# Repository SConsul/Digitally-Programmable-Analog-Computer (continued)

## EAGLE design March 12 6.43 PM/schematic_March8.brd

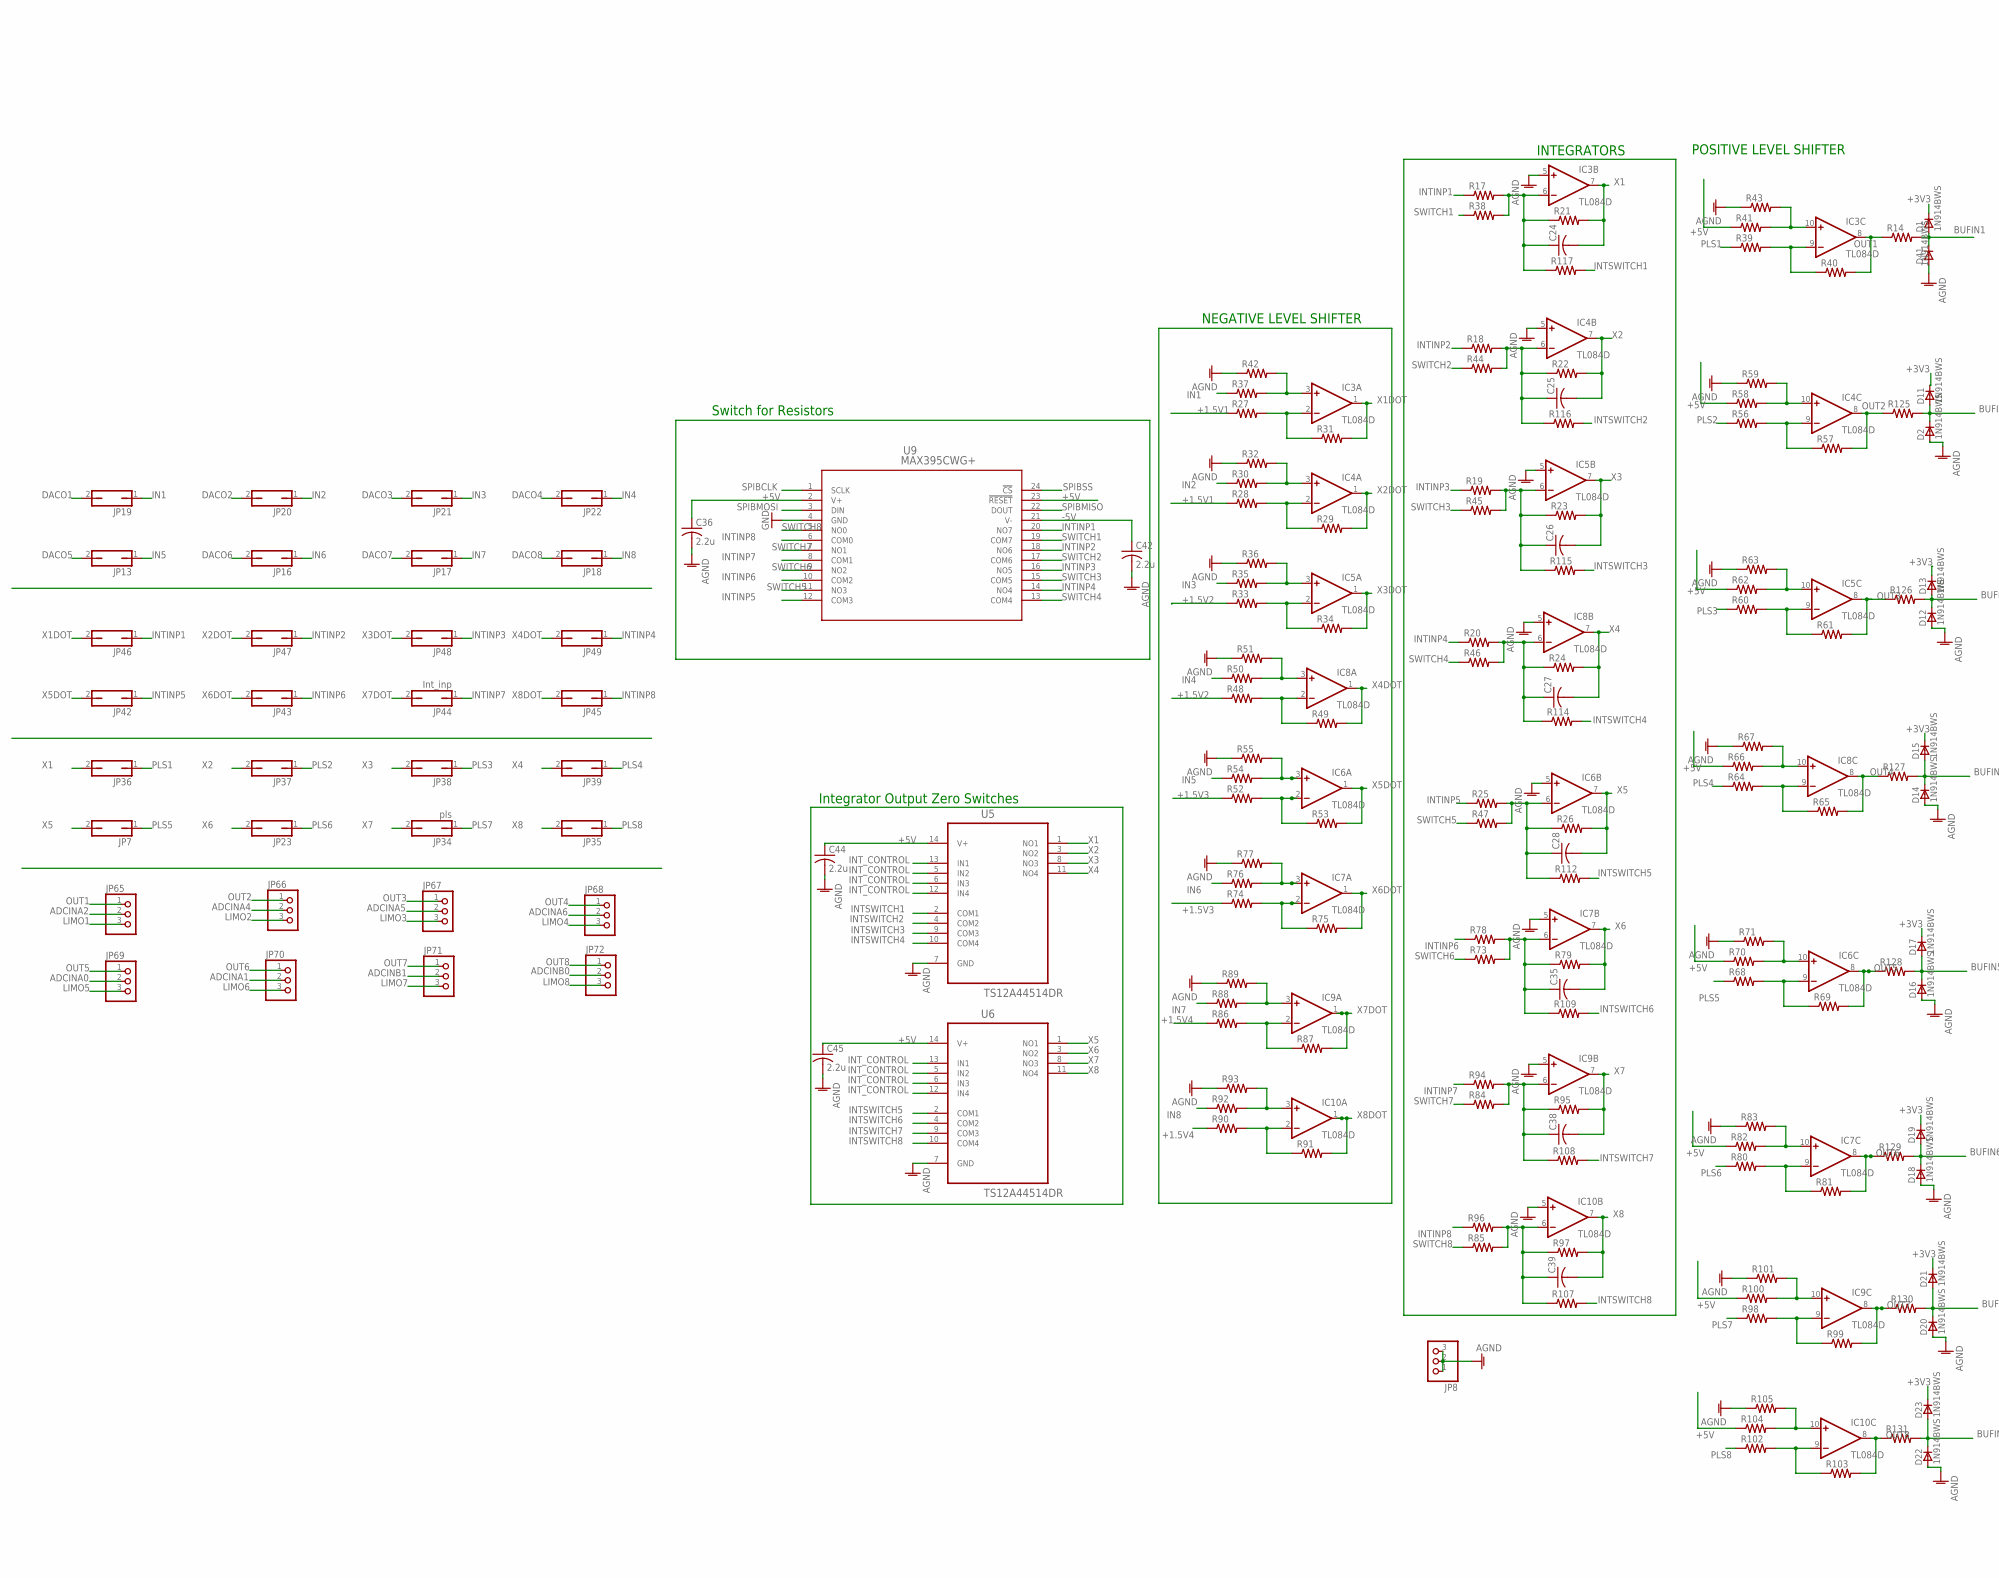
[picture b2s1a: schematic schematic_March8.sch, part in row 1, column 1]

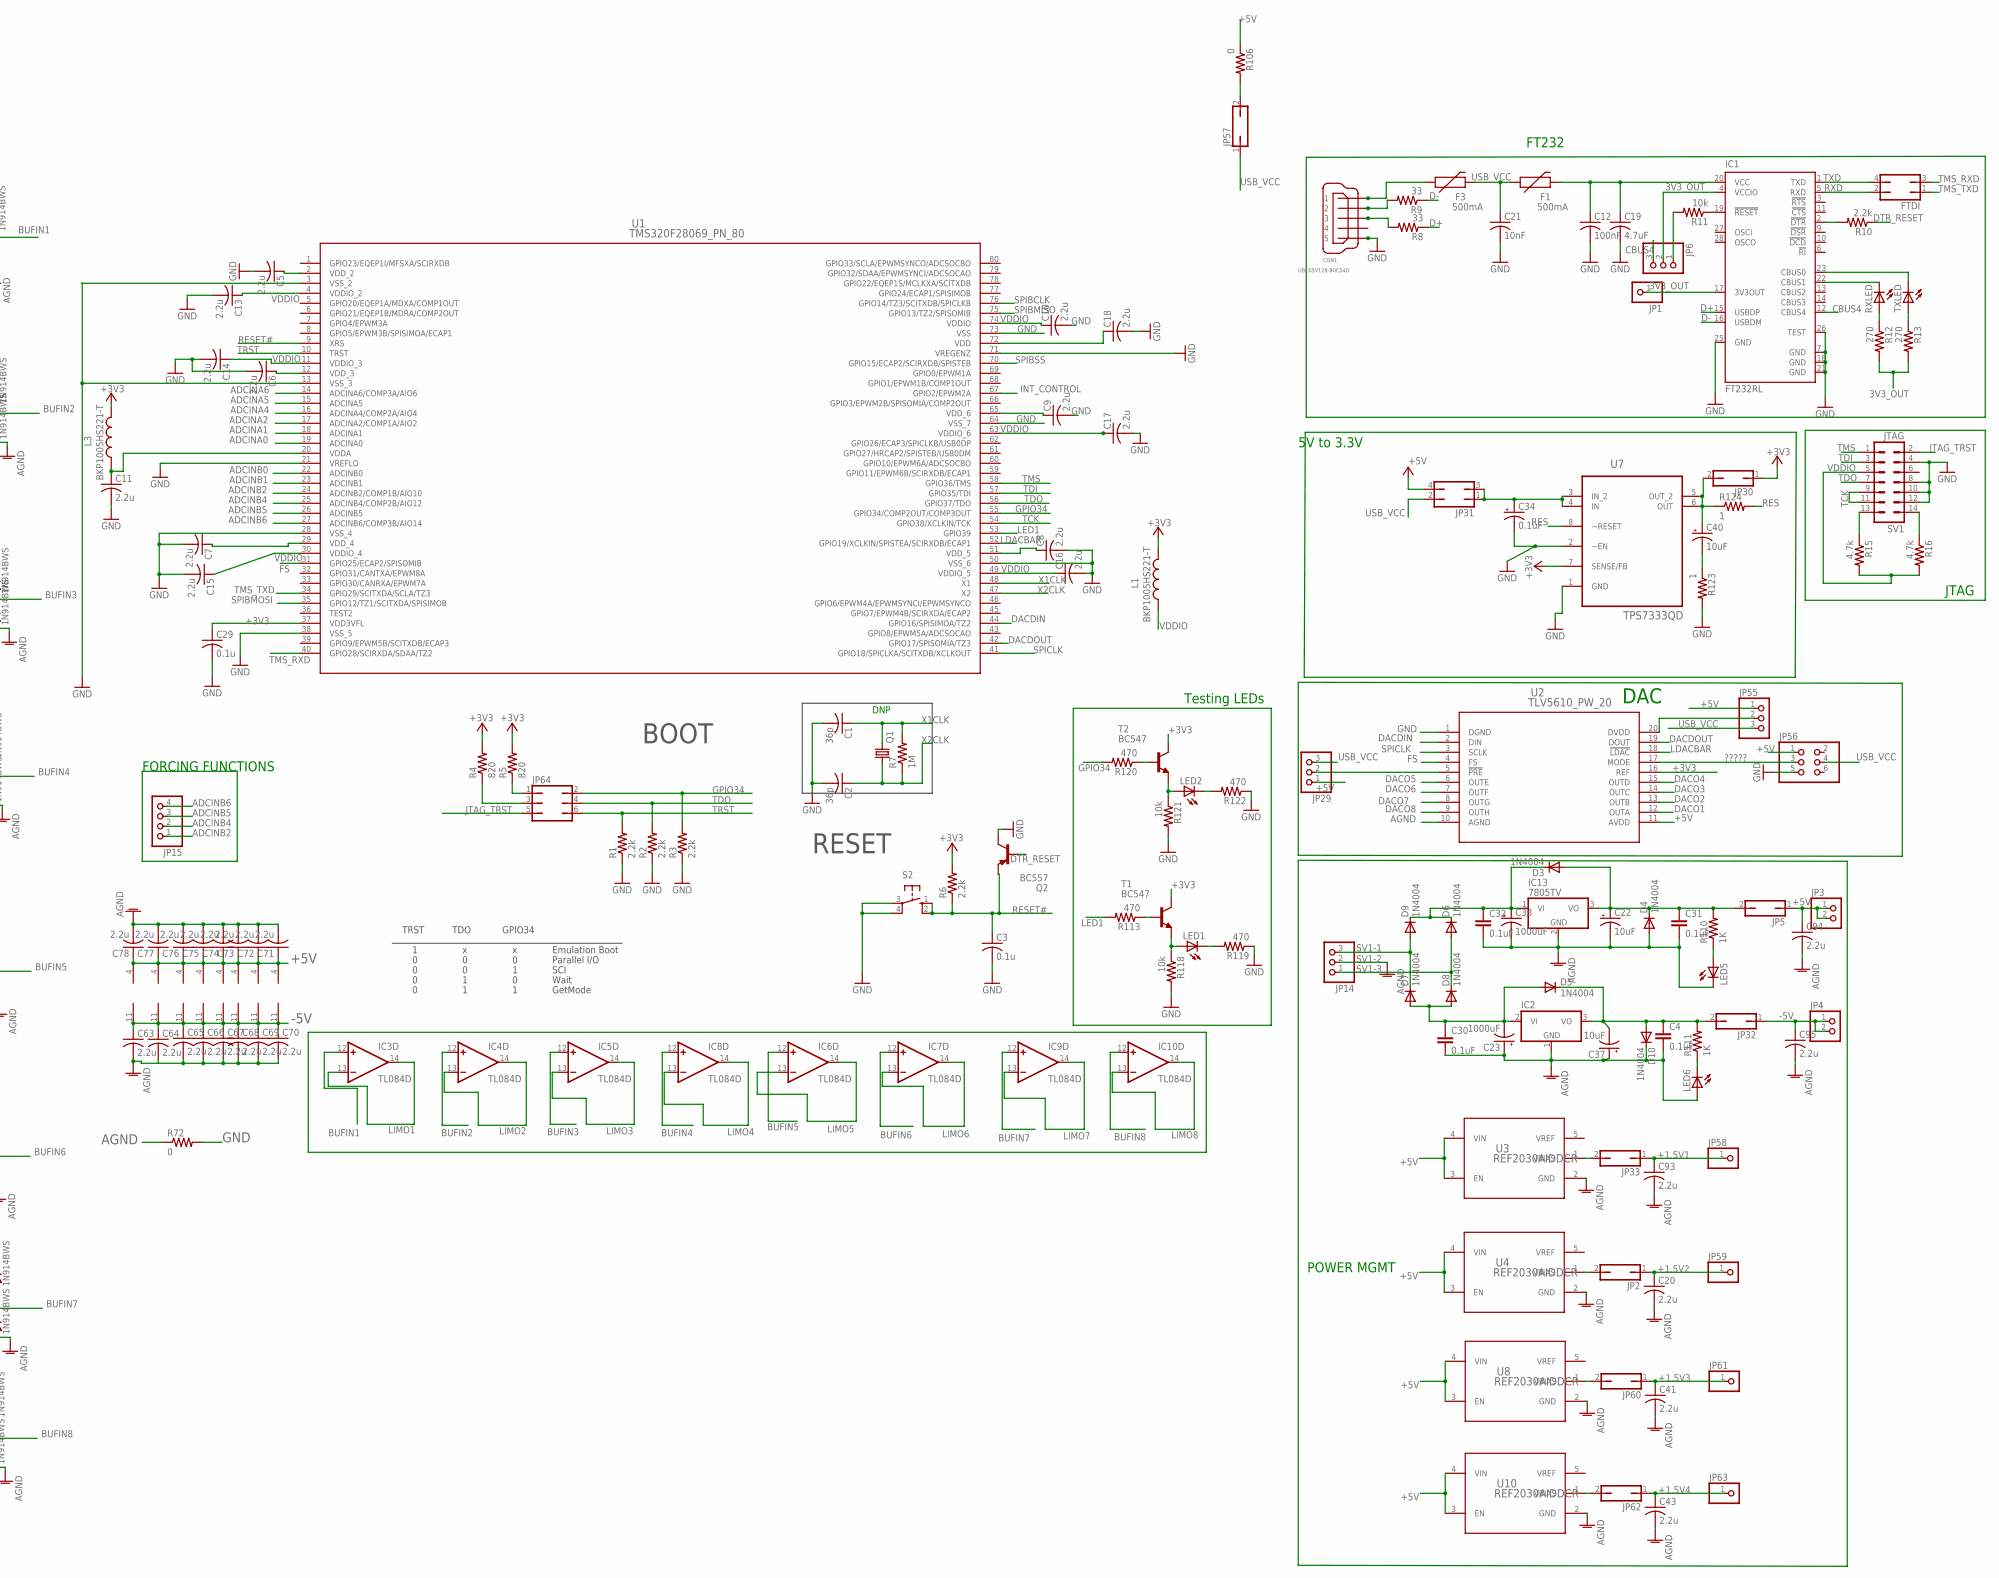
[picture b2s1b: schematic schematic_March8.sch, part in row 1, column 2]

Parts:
C1, C2: 36p; C1206
C3, C29: 0.1u; C1206
C4, C30, C31, C32: 0.1uF; C1206
C5, C6, C7, C8, C9, C10, C11, C13, C14, C15, C16, C17, C18, C20, C36, C41, C42, C43, C44, C45, C63, C64, C65, C66, C67, C68, C69, C70, C71, C72, C73, C74, C75, C76, C77, C78, C93, C94, C95: 2.2u; C1206
C12: 100nF; C1206
C19: 4.7uF; C1206
C21: 10nF; C1206
C22, C37, C40: 10uF; E2,5-7
C23, C33: 1000uF; E2,5-7
C24, C25, C26, C27, C28, C35, C38, C39: C-USC1206; C1206
C34: 0.1uF; E2,5-7
CON1: UBC05V128-B0C04D; 32005-201
D1, D2, D11, D12, D13, D14, D15, D16, D17, D18, D19, D20, D21, D22, D23, D41: 1N914BWS; SOD323F
D3, D4, D5, D6, D7, D8, D9, D10: 1N4004; DO41-10
F1, F3: 500mA; 0603
FTDI: JP2Q
IC1: FT232RL; SSOP28
IC2: 7905T; TO220H
IC3, IC4, IC5, IC6, IC7, IC8, IC9, IC10: TL084D; SO14
IC13: 7805TV; TO220V
JP1, JP58, JP59, JP61, JP63: PINHD-1X1; 1X01
JP2, JP5, JP7, JP13, JP16, JP17, JP18, JP19, JP20, JP21, JP22, JP23, JP30, JP32, JP33, JP35, JP36, JP37, JP38, JP39, JP42, JP43, JP45, JP46, JP47, JP48, JP49, JP57, JP60, JP62: JP1Q; JP1
JP3, JP4: PINHD-1X2; 1X02
JP6, JP8, JP14, JP29, JP55, JP65, JP66, JP67, JP68, JP69, JP70, JP71, JP72: PINHD-1X3; 1X03
JP15: PINHD-1X4; 1X04
JP31: JP2Q
JP34: pls; JP1
JP44: Int_inp; JP1
JP56: PINHD-2X3; 2X03
JP64: JP3Q
L1, L3: BKP1005HS221-T; 0204/5
LED1, LED2, LED5, LED6: LED3MM
Q1: CRYSTALHC49S; HC49/S
Q2: BC557; TO92-EBC
R1, R2, R3, R6, R10: 2.2k; R1206
R4, R5: 820; R1206
R7: 1M; R1206
R8, R9: 33; R1206
R11, R118, R121: 10k; R1206
R12, R13: 270; R1206
R14, R17, R18, R19, R20, R21, R22, R23, R24, R25, R26, R27, R28, R29, R30, R31, R32, R33, R34, R35, R36, R37, R38, R39, R40, R41, R42, R43, R44, R45, R46, R47, R48, R49, R50, R51, R52, R53, R54, R55, R56, R57, R58, R59, R60, R61, R62, R63, R64, R65, R66, R67, R68, R69, R70, R71, R73, R74, R75, R76, R77, R78, R79, R80, R81, R82, R83, R84, R85, R86, R87, R88, R89, R90, R91, R92, R93, R94, R95, R96, R97, R98, R99, R100, R101, R102, R103, R104, R105, R107, R108, R109, R112, R114, R115, R116, R117, R125, R126, R127, R128, R129, R130, R131: R-US_R1206; R1206
R15, R16: 4.7k; M1206
R72, R106: 0; R1206
R110, R111: 1K; 0207/10
R113, R119, R120, R122: 470; R1206
R123, R124: 1; M1206
RXLED: LEDCHIPLED_1206; CHIPLED_1206
S2: 10-XX; B3F-10XX
SV1: JTAG; MA07-2
T1, T2: BC547; TO92
TXLED: LEDCHIPLED_1206; CHIPLED_1206
U1: TMS320F28069_PN_80; PN80
U2: TLV5610_PW_20; PW20
U3, U4, U8, U10: REF2030AIDDCR; DDC0005A_N
U5, U6: TS12A44514DR; SOIC127P600X175-14N
U7: TPS7333QD; SOIC127P600X175-8N
U9: MAX395CWG+; 21-0042B_24

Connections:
3V3_OUT: IC1.4 (VCCIO), IC1.17 (3V3OUT), JP1.1, JP6.2, R12.2, R13.2
+1.5V1: C93.1, JP33.1, JP58.1, R27.1, R28.1
+1.5V2: C20.1, JP2.1, JP59.1, R33.1, R48.1
+1.5V3: C41.1, JP60.1, JP61.1, R52.1, R74.1
+1.5V4: C43.1, JP62.1, JP63.1, R86.1, R90.1
+3V3: C29.1, D1.C, D11.C, D13.C, D15.C, D17.C, D19.C, D21.C, D23.C, JP30.1, L1.2, L3.2, R4.2, R5.2, R6.2, T1.3 (C), T2.3 (C), U1.37 (VDD3VFL), U2.16 (REF), U7.7 (SENSE/FB)
+5V: C36.1, C44.1, C45.1, C71.1, C72.1, C73.1, C74.1, C75.1, C76.1, C77.1, C78.1, C94.1, IC3.4 (V+), IC4.4 (V+), IC5.4 (V+), IC6.4 (V+), IC7.4 (V+), IC8.4 (V+), IC9.4 (V+), IC10.4 (V+), JP3.1, JP3.2, JP5.1, JP29.1, JP31.4, JP55.1, JP56.1, R41.1, R58.1, R62.1, R66.1, R70.1, R82.1, R100.1, R104.1, R106.1, U2.11 (AVDD), U3.3 (EN), U3.4 (VIN), U4.3 (EN), U4.4 (VIN), U5.14 (V+), U6.14 (V+), U8.3 (EN), U8.4 (VIN), U9.2 (V+), U9.23 (!RESET), U10.3 (EN), U10.4 (VIN)
-5V: C42.1, C63.1, C64.1, C65.1, C66.1, C67.1, C68.1, C69.1, C70.1, C95.1, IC3.11 (V-), IC4.11 (V-), IC5.11 (V-), IC6.11 (V-), IC7.11 (V-), IC8.11 (V-), IC9.11 (V-), IC10.11 (V-), JP4.1, JP4.2, JP32.1, U9.21 (V-)
?????: JP56.3, U2.17 (MODE)
ADCINA0: JP69.2, U1.19 (ADCINA0)
ADCINA1: JP70.2, U1.18 (ADCINA1)
ADCINA2: JP65.2, U1.17 (ADCINA2/COMP1A/AIO2)
ADCINA4: JP66.2, U1.16 (ADCINA4/COMP2A/AIO4)
ADCINA5: JP67.2, U1.15 (ADCINA5)
ADCINA6: JP68.2, U1.14 (ADCINA6/COMP3A/AIO6)
ADCINB0: JP72.2, U1.22 (ADCINB0)
ADCINB1: JP71.2, U1.23 (ADCINB1)
ADCINB2: JP15.1, U1.24 (ADCINB2/COMP1B/AIO10)
ADCINB4: JP15.2, U1.25 (ADCINB4/COMP2B/AIO12)
ADCINB5: JP15.3, U1.26 (ADCINB5)
ADCINB6: JP15.4, U1.27 (ADCINB6/COMP3B/AIO14)
AGND: C4.2, C20.2, C22.-, C23.+, C30.2, C31.2, C32.2, C33.-, C36.2, C37.+, C41.2, C42.2, C43.2, C44.2, C45.2, C63.2, C64.2, C65.2, C66.2, C67.2, C68.2, C69.2, C70.2, C71.2, C72.2, C73.2, C74.2, C75.2, C76.2, C77.2, C78.2, C93.2, C94.2, C95.2, D2.A, D4.A, D10.C, D12.A, D14.A, D16.A, D18.A, D20.A, D22.A, D41.A, IC2.1 (GND), IC3.5 (+IN), IC4.5 (+IN), IC5.5 (+IN), IC6.5 (+IN), IC7.5 (+IN), IC8.5 (+IN), IC9.5 (+IN), IC10.5 (+IN), IC13.2 (GND), JP8.1, JP8.2, JP8.3, LED5.K (C), LED6.A, R32.1, R36.1, R42.1, R43.1, R51.1, R55.1, R59.1, R63.1, R67.1, R71.1, R72.1, R77.1, R83.1, R89.1, R93.1, R101.1, R105.1, U2.10 (AGND), U3.2 (GND), U4.2 (GND), U5.7 (GND), U6.7 (GND), U8.2 (GND), U10.2 (GND)
BUFIN1: D1.A, D41.C, IC3.12 (+IN), R14.2
BUFIN2: D2.C, D11.A, IC4.12 (+IN), R125.2
BUFIN3: D12.C, D13.A, IC5.12 (+IN), R126.2
BUFIN4: D14.C, D15.A, IC8.12 (+IN), R127.2
BUFIN5: D16.C, D17.A, IC6.12 (+IN), R128.2
BUFIN6: D18.C, D19.A, IC7.12 (+IN), R129.2
BUFIN7: D20.C, D21.A, IC9.12 (+IN), R130.2
BUFIN8: D22.C, D23.A, IC10.12 (+IN), R131.2
CBUS4: IC1.12 (CBUS4), JP6.3
D+: IC1.15 (USBDP), R8.1
D-: IC1.16 (USBDM), R9.1
DACDIN: U1.44 (GPIO16/SPISIMOA/TZ2), U2.2 (DIN)
DACDOUT: U1.42 (GPIO17/SPISOMIA/TZ3), U2.19 (DOUT)
DACO1: JP19.2, U2.12 (OUTA)
DACO2: JP20.2, U2.13 (OUTB)
DACO3: JP21.2, U2.14 (OUTC)
DACO4: JP22.2, U2.15 (OUTD)
DACO5: JP13.2, U2.6 (OUTE)
DACO6: JP16.2, U2.7 (OUTF)
DACO7: JP17.2, U2.8 (OUTG)
DACO8: JP18.2, U2.9 (OUTH)
DTR_RESET: Q2.B, R10.1
FS: U1.31 (GPIO25/ECAP2/SPISOMIB), U2.4 (FS)
GND: C1.2, C2.2, C3.2, C5.2, C6.2, C7.2, C8.2, C9.2, C10.2, C11.2, C12.2, C13.2, C14.2, C15.2, C16.2, C17.2, C18.2, C19.2, C21.2, C29.2, C34.-, CON1.5, IC1.7 (GND), IC1.18 (GND), IC1.21 (GND), IC1.25 (GND), IC1.26 (TEST), JP56.5, Q2.C, R1.1, R2.1, R3.1, R72.2, R118.2, R119.1, R121.2, R122.1, R123.2, S2.3, S2.4 (P1), SV1.4, SV1.8, SV1.10, SV1.12, U1.3 (VSS_2), U1.13 (VSS_3), U1.21 (VREFLO), U1.28 (VSS_4), U1.38 (VSS_5), U1.50 (VSS_6), U1.64 (VSS_7), U1.71 (VREGENZ), U1.73 (VSS), U2.1 (DGND), U7.1 (GND), U7.2 (~EN), U9.4 (GND)
GPIO34: JP64.2, R3.2, R120.2, U1.55 (GPIO34/COMP2OUT/COMP3OUT)
IDK: C22.+, C31.1, D3.A, D4.C, IC13.3 (VO), JP5.2, R110.2
IDK2: C4.1, C37.-, D5.C, D10.A, IC2.3 (VO), JP32.2, R111.2
IN1: JP19.1, R37.1
IN2: JP20.1, R30.1
IN3: JP21.1, R35.1
IN4: JP22.1, R50.1
IN5: JP13.1, R54.1
IN6: JP16.1, R76.1
IN7: JP17.1, R88.1
IN8: JP18.1, R92.1
INTINP1: JP46.1, R17.1, U9.20 (NO7)
INTINP2: JP47.1, R18.1, U9.18 (NO6)
INTINP3: JP48.1, R19.1, U9.16 (NO5)
INTINP4: JP49.1, R20.1, U9.14 (NO4)
INTINP5: JP42.1, R25.1, U9.12 (COM3)
INTINP6: JP43.1, R78.1, U9.10 (COM2)
INTINP7: JP44.1, R94.1, U9.8 (COM1)
INTINP8: JP45.1, R96.1, U9.6 (COM0)
INTSWITCH1: R117.2, U5.2 (COM1)
INTSWITCH2: R116.2, U5.4 (COM2)
INTSWITCH3: R115.2, U5.9 (COM3)
INTSWITCH4: R114.2, U5.10 (COM4)
INTSWITCH5: R112.2, U6.2 (COM1)
INTSWITCH6: R109.2, U6.4 (COM2)
INTSWITCH7: R108.2, U6.9 (COM3)
INTSWITCH8: R107.2, U6.10 (COM4)
INT_CONTROL: U1.67 (GPIO2/EPWM2A), U5.5 (IN2), U5.6 (IN3), U5.12 (IN4), U5.13 (IN1), U6.5 (IN2), U6.6 (IN3), U6.12 (IN4), U6.13 (IN1)
JTAG_TRST: JP64.5, SV1.2
LDACBAR: U1.52 (GPIO19/XCLKIN/SPISTEA/SCIRXDB/ECAP1), U2.18 (!LDAC)
LED1: R113.2, U1.53 (GPIO39)
LIMO1: IC3.13 (-IN), IC3.14 (OUT), JP65.3
LIMO2: IC4.13 (-IN), IC4.14 (OUT), JP66.3
LIMO3: IC5.13 (-IN), IC5.14 (OUT), JP67.3
LIMO4: IC8.13 (-IN), IC8.14 (OUT), JP68.3
LIMO5: IC6.13 (-IN), IC6.14 (OUT), JP69.3
LIMO6: IC7.13 (-IN), IC7.14 (OUT), JP70.3
LIMO7: IC9.13 (-IN), IC9.14 (OUT), JP71.3
LIMO8: IC10.13 (-IN), IC10.14 (OUT), JP72.3
unnamed: C5.1, U1.2 (VDD_2)
unnamed: C6.1, U1.12 (VDD_3)
unnamed: C7.1, U1.29 (VDD_4)
unnamed: C8.1, U1.51 (VDD_5)
unnamed: C9.1, U1.65 (VDD_6)
unnamed: IC1.2 (!DTR), R10.2
unnamed: C11.1, L3.1, U1.20 (VDDA)
unnamed: C18.1, U1.72 (VDD)
unnamed: JP64.1, R5.1
unnamed: JP64.3, R4.1
unnamed: CON1.2, R9.2
unnamed: CON1.3, R8.2
unnamed: IC1.19 (!RESET), R11.1
unnamed: IC1.22 (CBUS1), RXLED.C
unnamed: IC1.23 (CBUS0), TXLED.C
unnamed: R12.1, RXLED.A
unnamed: R13.1, TXLED.A
unnamed: C25.1, IC4.6 (-IN), R18.2, R22.1, R44.2, R116.1
unnamed: C26.1, IC5.6 (-IN), R19.2, R23.1, R45.2, R115.1
unnamed: C27.1, IC8.6 (-IN), R20.2, R24.1, R46.2, R114.1
unnamed: IC4.2 (-IN), R28.2, R29.1
unnamed: R15.1, SV1.13
unnamed: R16.1, SV1.14
unnamed: IC4.3 (+IN), R30.2, R32.2
unnamed: C24.1, IC3.6 (-IN), R17.2, R21.1, R38.2, R117.1
unnamed: IC3.2 (-IN), R27.2, R31.1
unnamed: C28.1, IC6.6 (-IN), R25.2, R26.1, R47.2, R112.1
unnamed: IC5.2 (-IN), R33.2, R34.1
unnamed: IC3.3 (+IN), R37.2, R42.2
unnamed: IC5.3 (+IN), R35.2, R36.2
unnamed: IC3.9 (-IN), R39.2, R40.1
unnamed: IC3.10 (+IN), R41.2, R43.2
unnamed: IC8.2 (-IN), R48.2, R49.1
unnamed: IC8.3 (+IN), R50.2, R51.2
unnamed: IC7.2 (-IN), R74.2, R75.1
unnamed: IC6.2 (-IN), R52.2, R53.1
unnamed: IC6.3 (+IN), R54.2, R55.2
unnamed: IC7.3 (+IN), R76.2, R77.2
unnamed: IC4.9 (-IN), R56.2, R57.1
unnamed: IC4.10 (+IN), R58.2, R59.2
unnamed: IC5.9 (-IN), R60.2, R61.1
unnamed: IC5.10 (+IN), R62.2, R63.2
unnamed: IC8.9 (-IN), R64.2, R65.1
unnamed: IC8.10 (+IN), R66.2, R67.2
unnamed: IC6.9 (-IN), R68.2, R69.1
unnamed: IC6.10 (+IN), R70.2, R71.2
unnamed: C35.1, IC7.6 (-IN), R73.2, R78.2, R79.1, R109.1
unnamed: IC7.9 (-IN), R80.2, R81.1
unnamed: IC7.10 (+IN), R82.2, R83.2
unnamed: IC9.2 (-IN), R86.2, R87.1
unnamed: IC9.3 (+IN), R88.2, R89.2
unnamed: IC10.2 (-IN), R90.2, R91.1
unnamed: IC10.3 (+IN), R92.2, R93.2
unnamed: C38.1, IC9.6 (-IN), R84.2, R94.2, R95.1, R108.1
unnamed: C39.1, IC10.6 (-IN), R85.2, R96.2, R97.1, R107.1
unnamed: IC9.9 (-IN), R98.2, R99.1
unnamed: IC9.10 (+IN), R100.2, R101.2
unnamed: IC10.9 (-IN), R102.2, R103.1
unnamed: IC10.10 (+IN), R104.2, R105.2
unnamed: C32.1, C33.+, D3.C, D6.C, D9.C, IC13.1 (VI)
unnamed: C40.+, JP30.2, R124.1, U7.5 (OUT_2), U7.6 (OUT)
unnamed: C40.-, R123.1
unnamed: LED6.K (C), R111.1
unnamed: C34.+, JP31.1, JP31.3, U7.3 (IN_2), U7.4 (IN)
unnamed: LED5.A, R110.1
unnamed: CON1.1, F3.1
unnamed: C23.-, C30.1, D5.A, D7.A, D8.A, IC2.2 (VI)
unnamed: JP33.2, U3.1 (VBIAS)
unnamed: JP6.1, R11.2
unnamed: R113.1, T1.2 (B)
unnamed: LED1.A, R118.1, T1.1 (E)
unnamed: LED1.K (C), R119.2
unnamed: R120.1, T2.2 (B)
unnamed: LED2.A, R121.1, T2.1 (E)
unnamed: LED2.K (C), R122.2
unnamed: JP55.2, U2.20 (DVDD)
unnamed: JP2.2, U4.1 (VBIAS)
unnamed: JP29.2, U2.5 (!PRE)
unnamed: JP57.2, R106.2
unnamed: JP60.2, U8.1 (VBIAS)
unnamed: JP62.2, U10.1 (VBIAS)
OUT1: IC3.8 (OUT), JP65.1, R14.1, R40.2
OUT2: IC4.8 (OUT), JP66.1, R57.2, R125.1
OUT3: IC5.8 (OUT), JP67.1, R61.2, R126.1
OUT4: IC8.8 (OUT), JP68.1, R65.2, R127.1
OUT5: IC6.8 (OUT), JP69.1, R69.2, R128.1
OUT6: IC7.8 (OUT), JP70.1, R81.2, R129.1
OUT7: IC9.8 (OUT), JP71.1, R99.2, R130.1
OUT8: IC10.8 (OUT), JP72.1, R103.2, R131.1
PLS1: JP36.1, R39.1
PLS2: JP37.1, R56.1
PLS3: JP38.1, R60.1
PLS4: JP39.1, R64.1
PLS5: JP7.1, R68.1
PLS6: JP23.1, R80.1
PLS7: JP34.1, R98.1
PLS8: JP35.1, R102.1
RES: R124.2, U7.8 (~RESET)
RESET#: C3.1, Q2.E, R6.1, S2.1 (S), S2.2 (S1), U1.9 (XRS)
RXD: FTDI.2, IC1.5 (RXD)
SPIBCLK: U1.76 (GPIO14/TZ3/SCITXDB/SPICLKB), U9.1 (SCLK)
SPIBMISO: U1.75 (GPIO13/TZ2/SPISOMIB), U9.22 (DOUT)
SPIBMOSI: U1.35 (GPIO12/TZ1/SCITXDA/SPISIMOB), U9.3 (DIN)
SPIBSS: U1.70 (GPIO15/ECAP2/SCIRXDB/SPISTEB), U9.24 (!CS)
SPICLK: U1.41 (GPIO18/SPICLKA/SCITXDB/XCLKOUT), U2.3 (SCLK)
SV1-1: D7.C, D9.A, JP14.3
SV1-2: JP14.2
SV1-3: D6.A, D8.C, JP14.1
SWITCH1: R38.1, U9.19 (COM7)
SWITCH2: R44.1, U9.17 (COM6)
SWITCH3: R45.1, U9.15 (COM5)
SWITCH4: R46.1, U9.13 (COM4)
SWITCH5: R47.1, U9.11 (NO3)
SWITCH6: R73.1, U9.9 (NO2)
SWITCH7: R84.1, U9.7 (NO1)
SWITCH8: R85.1, U9.5 (NO0)
TCK: SV1.9, SV1.11, U1.54 (GPIO38/XCLKIN/TCK)
TDI: SV1.3, U1.57 (GPIO35/TDI)
TDO: JP64.4, R2.2, SV1.7, U1.56 (GPIO37/TDO)
TMS: SV1.1, U1.58 (GPIO36/TMS)
TMS_RXD: FTDI.3, U1.40 (GPIO28/SCIRXDA/SDAA/TZ2)
TMS_TXD: FTDI.1, U1.34 (GPIO29/SCITXDA/SCLA/TZ3)
TRST: JP64.6, R1.2, U1.10 (TRST)
TXD: FTDI.4, IC1.1 (TXD)
USB_VCC: C21.1, F1.1, F3.2, JP29.3, JP31.2, JP55.3, JP56.4, JP57.1
VCC: C12.1, C19.1, F1.2, IC1.20 (VCC)
VDDIO: C10.1, C13.1, C14.1, C15.1, C16.1, C17.1, L1.1, R15.2, R16.2, SV1.5, U1.4 (VDDIO_2), U1.11 (VDDIO_3), U1.30 (VDDIO_4), U1.49 (VDDIO_5), U1.63 (VDDIO_6), U1.74 (VDDIO)
X1: C24.2, IC3.7 (OUT), JP36.2, R21.2, U5.1 (NO1)
X1CLK: C1.1, Q1.2, R7.2, U1.48 (X1)
X1DOT: IC3.1 (OUT), JP46.2, R31.2
X2: C25.2, IC4.7 (OUT), JP37.2, R22.2, U5.3 (NO2)
X2CLK: C2.1, Q1.1, R7.1, U1.47 (X2)
X2DOT: IC4.1 (OUT), JP47.2, R29.2
X3: C26.2, IC5.7 (OUT), JP38.2, R23.2, U5.8 (NO3)
X3DOT: IC5.1 (OUT), JP48.2, R34.2
X4: C27.2, IC8.7 (OUT), JP39.2, R24.2, U5.11 (NO4)
X4DOT: IC8.1 (OUT), JP49.2, R49.2
X5: C28.2, IC6.7 (OUT), JP7.2, R26.2, U6.1 (NO1)
X5DOT: IC6.1 (OUT), JP42.2, R53.2
X6: C35.2, IC7.7 (OUT), JP23.2, R79.2, U6.3 (NO2)
X6DOT: IC7.1 (OUT), JP43.2, R75.2
X7: C38.2, IC9.7 (OUT), JP34.2, R95.2, U6.8 (NO3)
X7DOT: IC9.1 (OUT), JP44.2, R87.2
X8: C39.2, IC10.7 (OUT), JP35.2, R97.2, U6.11 (NO4)
X8DOT: IC10.1 (OUT), JP45.2, R91.2

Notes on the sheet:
TDO
GPIO34
TRST
Emulation Boot
Parallel I/O
SCI
Wait
GetMode
BOOT
RESET
DNP
INTEGRATORS
NEGATIVE LEVEL SHIFTER
POSITIVE LEVEL SHIFTER
FT232
5V to 3.3V
JTAG
DAC
FORCING FUNCTIONS
POWER MGMT
Integrator Output Zero Switches
Testing LEDs
Switch for Resistors

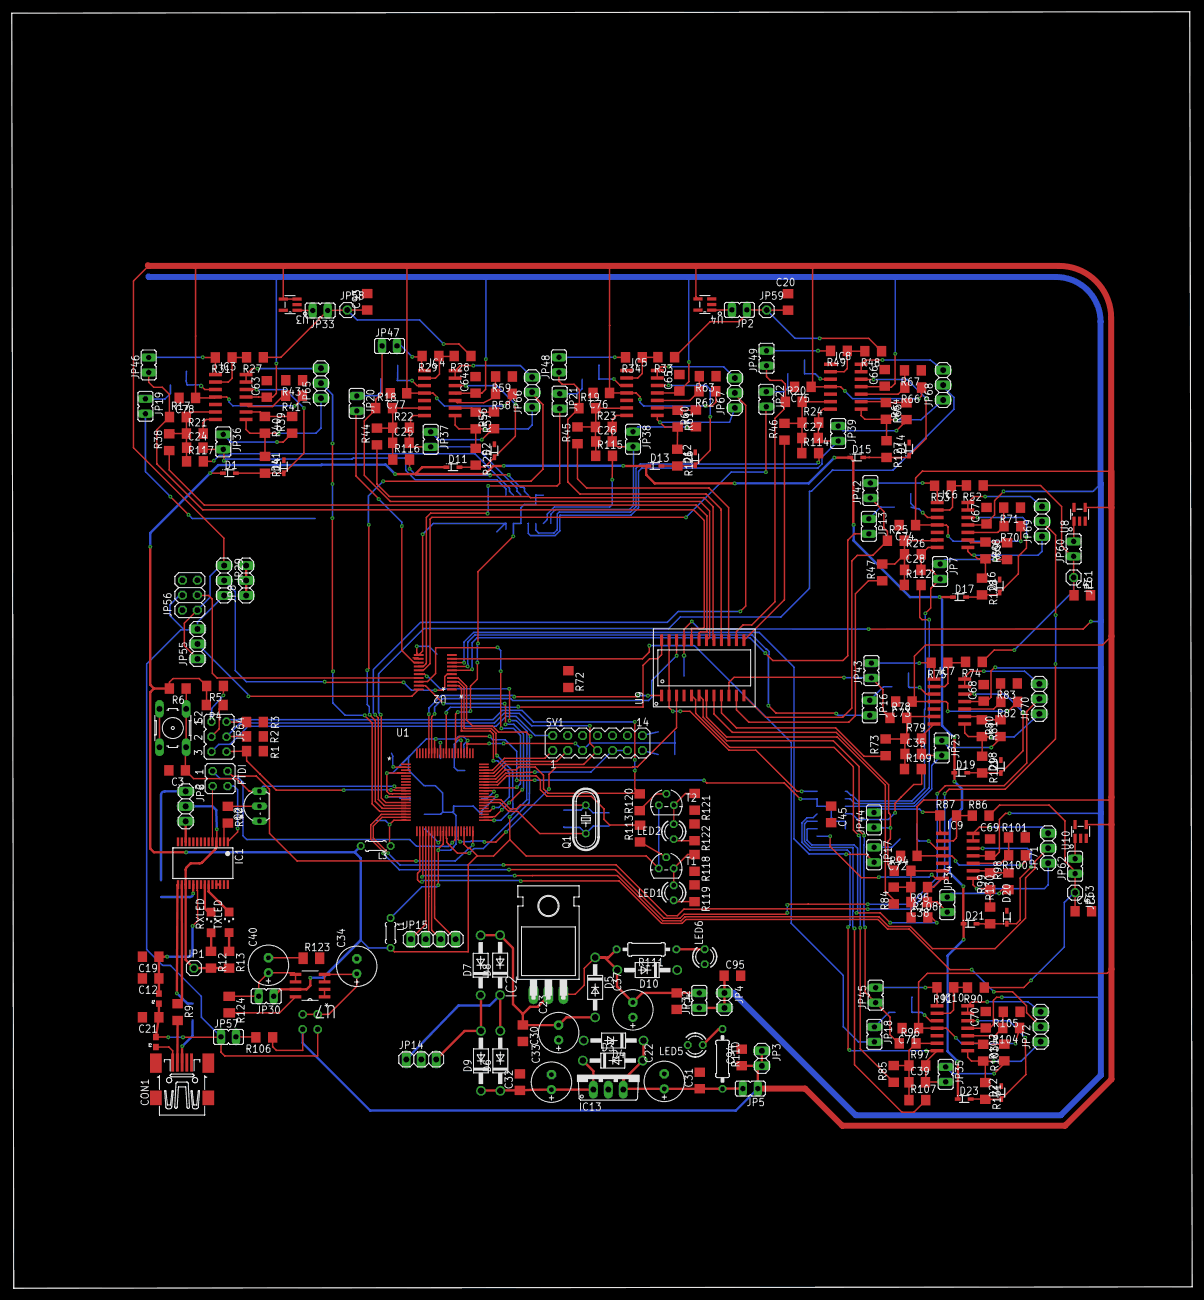
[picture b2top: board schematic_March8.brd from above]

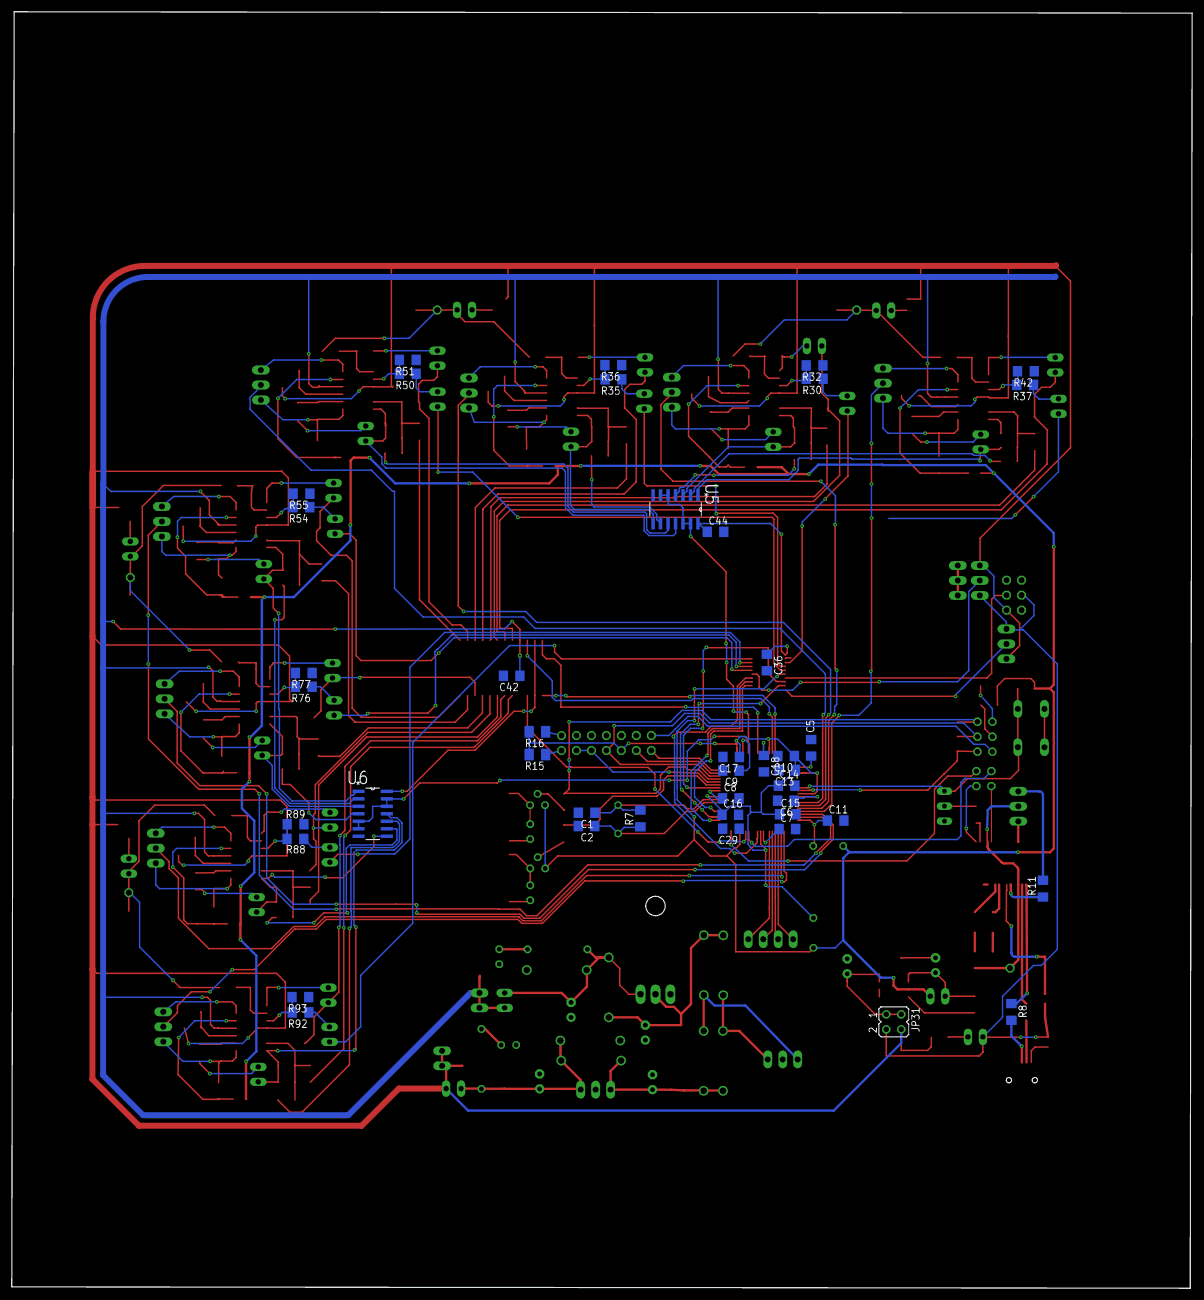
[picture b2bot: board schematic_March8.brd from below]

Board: 2 copper layers, 200.3 x 216.6 mm, 314 parts (43 on the bottom side), 229 nets.

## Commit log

2019-03-07 Add files via upload
    To begin routing
2019-03-07 added pinhd for DAC mode
2019-03-08 modified limiting circuit
2019-03-08 Routing of digital parts
2019-03-08 Limiter Circuit Added
    Added new limiting circuit with Zener and diode. Provided 1x3 jumpers to choose the circuit with or without the limiters
2019-03-09 Added buffer in limiter circuit (Folder March 9)
2019-03-09 Began digital part ka routing
2019-03-09 analog routing in progress
2019-03-10 Completed routing of analog part
2019-03-10 Continued digital routing
2019-03-10 Done digital (except switches and ADC inputs)
2019-03-10 Analog internal routing
2019-03-11 Began interconnecting Analog and digital parts
2019-03-11 rearranged pcb components
2019-03-11 Continued Parth's design
2019-03-12 Connecting some more dots
2019-03-12 Near Completion
2019-03-12 Completed board
2019-03-12 After implementing Sir's limiter circuit
2019-03-12 Brought components closer
2019-03-13 Changed all 10mil lines to 12mil width
    Had to correct *358* DRC errors, a commendable feat which I think deserves a treat from the rest of the team
2019-03-15 Rearranged analog part to make the board smaller
2019-03-15 Rearranged Stuff
    Remaining - Ground Plane, Names, holes at the side, text (
2019-03-15 fixed schematic bugs
2019-03-15 Grounding complete
2019-03-16 added component value and names
2019-03-16 Adding working code for ADC and DAC for launchpad till Evaluation 2
2019-03-16 name placement done
2019-03-16 changed LED to SMD, moved USB-hd
2019-03-17 Minor corrections in DAC connections, decoupling placed for DAC
2019-03-17 Changed folder name to reflect timestamp
2019-03-25 Made corrections, added RC values
2019-04-02 Nothing New Here. Added Code test files.
2019-04-17 Adding final code, use spi_loopback example in c2000 ware
2019-04-20 added MATLAB simulations
2019-04-21 added triangular wave simulation
